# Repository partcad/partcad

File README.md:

# PartCAD <!-- omit in toc -->

**[PartCAD] is the programming language for manufacturable things.**

A package is a Git repository with a `partcad.yaml` that declares parts (CAD scripts or files), assemblies,
materials and requirements. PartCAD renders, tests, simulates, analyses and documents them, and produces the
bill of materials, the sourcing and the assembly instructions from that same source. Everything is text, so it
is versioned, reviewed and generated like software, by people and by AI agents.

[Documentation](https://partcad.readthedocs.io/) · [Website](https://partcad.org/) ·
[Demos](https://youtube.com/@PartCAD) · [Discord](https://discord.gg/h5qhbHtygj)

## Install

Pick one. Every option ends up with the same `pc` command line tool and the same packages.

| You have           | Install                                                                                                                                                                                                                              |
| ------------------ | ------------------------------------------------------------------------------------------------------------------------------------------------------------------------------------------------------------------------------------ |
| Nothing yet        | The **PartCAD IDE**: `curl -fsSL https://raw.githubusercontent.com/partcad/partcad/main/install.sh \| sh -s -- --ide`, or the Windows and macOS installers on the [releases page](https://github.com/partcad/partcad/releases) |
| Python             | `pip install -U partcad`                                                                                                                                                                                                             |
| Visual Studio Code | `code --install-extension PartCAD.partcad-official` ([marketplace](https://marketplace.visualstudio.com/items?itemName=PartCAD.partcad-official))                                                                                     |
| Claude Code        | `/plugin marketplace add partcad/partcad@plugin-dist`, then `/plugin install pc@partcad`, then `/pc:setup`                                                                                                                            |

The standalone command line tools without Python, the snap, the FreeCAD add-on, the MCP server for other AI
agents, and the per-OS notes are all in
[Installation](https://partcad.readthedocs.io/en/latest/installation.html).

## Try it

```shell
pc init                      # a package in the current directory, with agent skills for Claude Code and Cursor
pc ide view my_part          # show it in the Digital Thread of the IDE or the extension
pc render my_part            # SVG, PNG, DXF... from any angle
pc qual test                 # qualify: basic, topology (overlaps, untoleranced faces), simulation, plugins
pc instructions my_assembly  # the assembly instruction book, PDF or HTML, with the bill of materials
```

Or, in Claude Code, `/pc:gen a mounting bracket with four M4 holes`: the agent writes the CAD script, renders
it and checks the result against what was asked.

The [tutorial](https://partcad.readthedocs.io/en/latest/tutorial.html) walks through a first package, and
[`examples/`](https://github.com/partcad/partcad/tree/main/examples) has one directory per feature.

## What it does

- **Parts** from [CadQuery], [build123d], [OpenSCAD], [Chili3D], [SDF], STEP, BREP, IGES, STL, 3MF, OBJ, glTF,
  FreeCAD, Autodesk Fusion, SolidWorks, Autodesk Inventor, CATIA V5, ACIS and Creo View files, OpenUSD stages,
  height maps, lidar and other point clouds, voxel models (MagicaVoxel, binvox), [KiCad EDA] PCBs, and any format
  a plugin package adds ([SolidCraft], Rhino).
- **Assemblies and scenes** in Assembly YAML, URDF, or a STEP, Autodesk Fusion or Creo View file, with interfaces
  and mating as objects.
- **Outputs**: STEP, BREP, STL, 3MF, OBJ, IGES, glTF, URDF, Gazebo and MuJoCo worlds, 2D projections,
  dimensioned drawings, Markdown documentation and PDF or HTML instruction books.
- **Engineering**: FEA, modal, thermal and CFD analysis (`pc cae`), simulation in MuJoCo or Gazebo
  (`pc qual test --simulation`), 2.5D toolpaths (`pc cam`), and materials and manufacturing methods carried into the bill of
  materials.
- **Supply chain**: a Build vs Buy decision per line item, stock-based procurement for made parts, and
  automated purchasing from the command line.
- **AI agents**: Agent Skills for Claude Code and Cursor, an MCP server (`pc mcp`), and plain-text
  `--no-ansi` output on every command.
- **Caching** in memory, on disk, in memcached and in S3, so a team or a CI fleet renders each model once.

The full list of what is supported, and what is still in progress, is in
[Supported formats and features](https://partcad.readthedocs.io/en/latest/supported.html).

## Why

PartCAD is not a drawing tool. It is the layer under the drawing tools: the specification of a manufacturable
product, kept in a form that a human, a CI job and an AI model can all read, change and verify. Keeping that
specification on-prem, in Git, and portable between CAD tools and manufacturers is the point. See
[Introduction](https://partcad.readthedocs.io/en/latest/intro.html) and
[Use cases](https://partcad.readthedocs.io/en/latest/use_cases.html).

## Community

Questions and feedback go to [Discord](https://discord.gg/h5qhbHtygj); bugs and ideas to
[GitHub issues](https://github.com/partcad/partcad/issues). Follow [LinkedIn], [YouTube] and [Twitter/X] for
releases. To contribute, start with
[Contributing](https://partcad.readthedocs.io/en/latest/contributing.html).

Licensed under [Apache 2.0](https://github.com/partcad/partcad/blob/main/LICENSE.txt).

<!-- mcp-name: io.github.partcad/partcad -->

[PartCAD]: https://partcad.org/
[LinkedIn]: https://linkedin.com/company/partcad
[YouTube]: https://youtube.com/@PartCAD
[Twitter/X]: https://x.com/PartCAD
[CadQuery]: https://github.com/CadQuery/cadquery
[build123d]: https://github.com/gumyr/build123d
[Chili3D]: https://github.com/xiangechen/chili3d
[OpenSCAD]: https://openscad.org/
[SDF]: https://github.com/fogleman/sdf
[KiCad EDA]: https://www.kicad.org/
[SolidCraft]: https://github.com/bherbruck/solidcraft

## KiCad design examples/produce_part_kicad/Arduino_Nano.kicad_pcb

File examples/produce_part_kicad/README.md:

# //pub/examples/partcad/produce_part_kicad

Example of KiCad integration using Arduino Nano from KiCad Templates

## Parts

### Arduino_Nano

## Software

| Software | Version | File | Hash | Description |
| --- | --- | --- | --- | --- |
| arduino-cli-installer | 1.3.1 | `arduino-cli-install.sh` from [url](https://raw.githubusercontent.com/arduino/arduino-cli/08ff7e2b76b7cd6394c4d09420b10cf0592b4405/install.sh) | `sha256:dfa8aa41202a3752f1a716d56584c24e7e93087b94c4ae8c50df50012ea6095d` | The official installer for arduino-cli, the host-side tool this board is programmed with. Not carried by this package: it is fetched from Arduino's own repository, at the commit tagged 1.3.1. |

<br/><br/>

*Generated by [PartCAD](https://partcad.org/)*

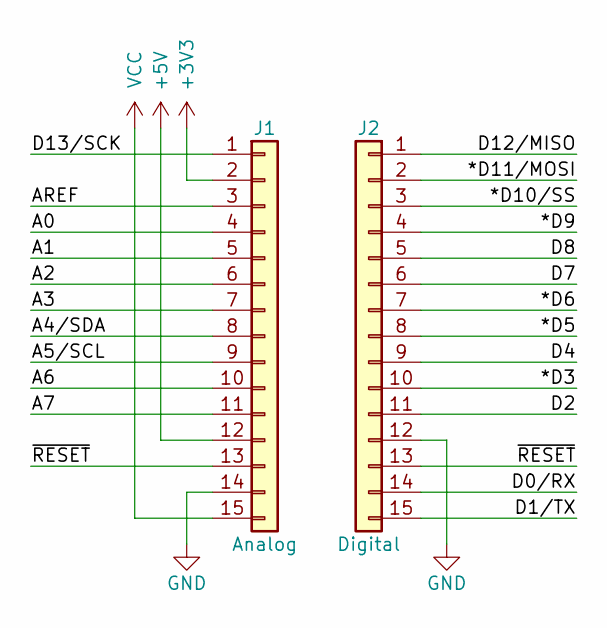
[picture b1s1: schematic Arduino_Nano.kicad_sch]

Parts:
J1: Analog; PinHeader_1x15_P2.54mm_Vertical
J2: Digital; PinHeader_1x15_P2.54mm_Vertical

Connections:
+3V3: J1.2
+5V: J1.12
/*D3: J2.10
/*D5: J2.8
/*D6: J2.7
/*D9: J2.4
/*D10/SS: J2.3
/*D11/MOSI: J2.2
/A0: J1.4
/A1: J1.5
/A2: J1.6
/A3: J1.7
/A4/SDA: J1.8
/A5/SCL: J1.9
/A6: J1.10
/A7: J1.11
/AREF: J1.3
/D0/RX: J2.14
/D1/TX: J2.15
/D2: J2.11
/D4: J2.9
/D7: J2.6
/D8: J2.5
/D12/MISO: J2.1
/D13/SCK: J1.1
/~RESET: J1.13, J2.13
GND: J1.14, J2.12
VCC: J1.15

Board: 2 copper layers, 6 parts (2 on the bottom side), 2 nets, no tracks yet.

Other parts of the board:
MH1, MH2, MH3, MH4: MountingHole_65mil

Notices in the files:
README.md:
License: Apache 2.0
